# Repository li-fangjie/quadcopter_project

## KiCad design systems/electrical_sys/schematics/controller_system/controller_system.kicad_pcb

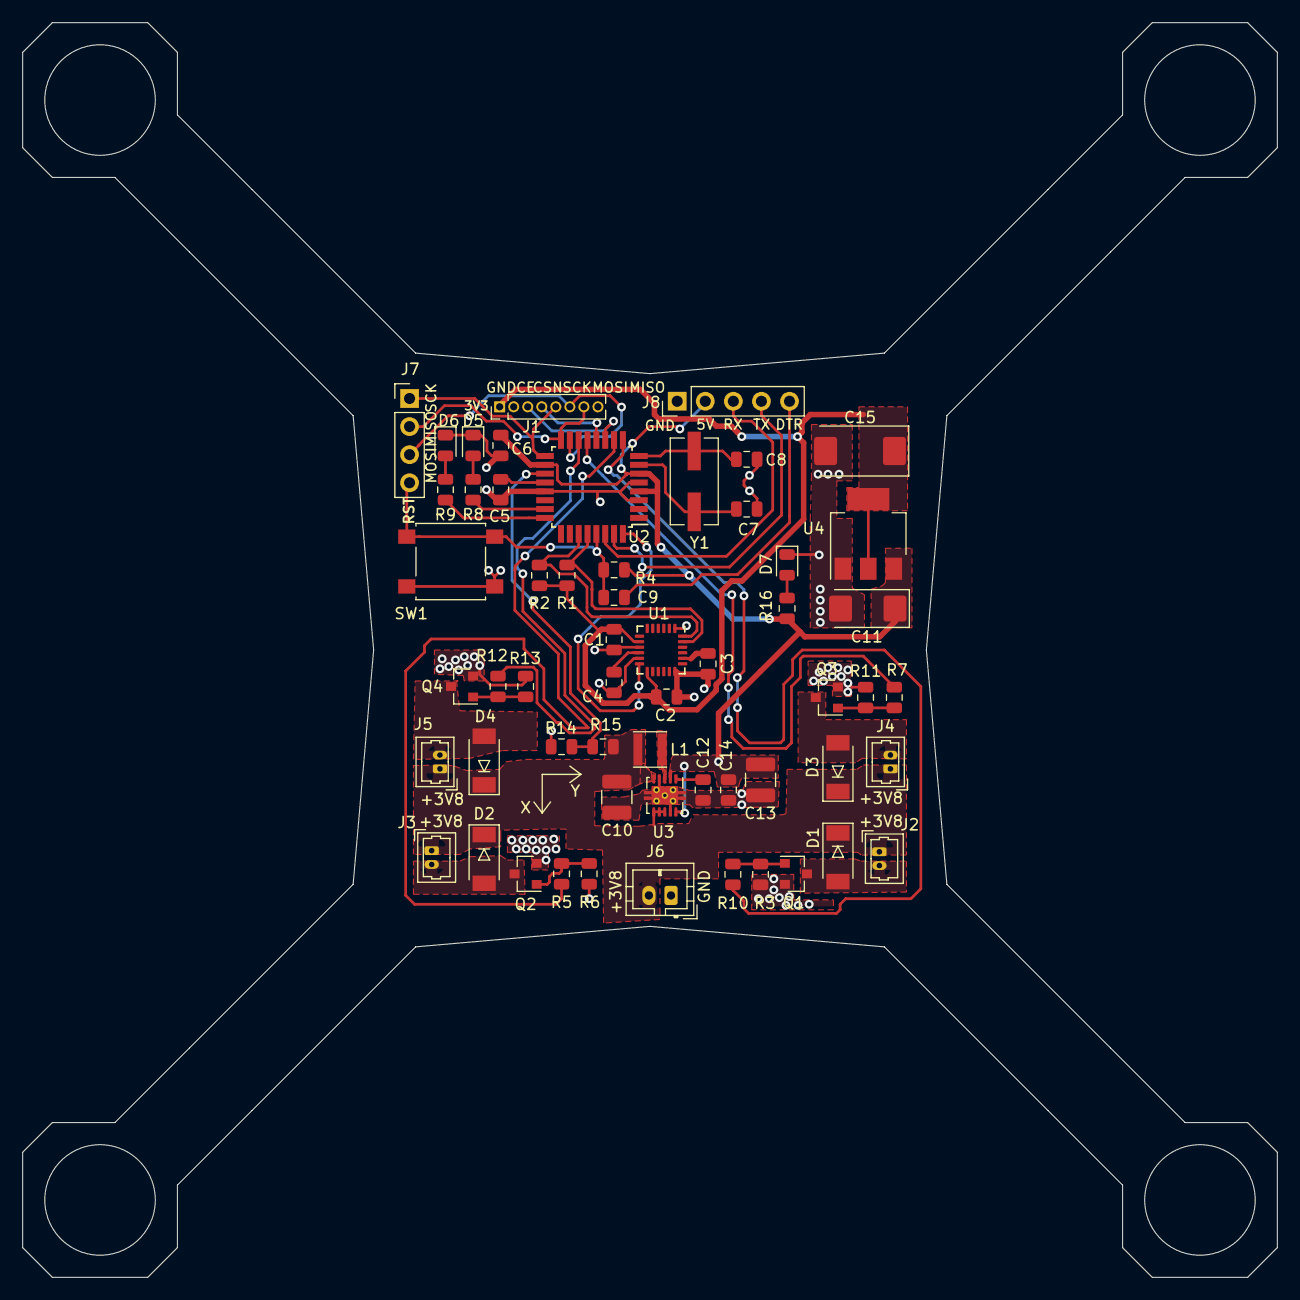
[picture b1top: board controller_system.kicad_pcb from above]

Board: 2 copper layers, 113.5 x 113.5 mm, 57 parts (0 on the bottom side), 41 nets.

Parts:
C1: 10 nF; C_0805_2012Metric
C2, C4, C5, C6, C9, C12, C14: 0.1 uF; C_0805_2012Metric
C3: 2.2 nF; C_0805_2012Metric
C7, C8: 22 pF; C_0805_2012Metric
C10: 10 uF; C_1210_3225Metric
C11: 10 uF; CP_EIA-6032-28_Kemet-C
C13: 22 uF; C_1210_3225Metric
C15: 22 uF; CP_EIA-7343-31_Kemet-D
D1, D2, D3, D4: D_Schottky; D_SOD-128
D5: LED_G; LED_0805_2012Metric
D6, D7: LED_R; LED_0805_2012Metric
J1: nRF24_Breakout; PinHeader_1x08_P1.27mm_Vertical
J2, J3, J4, J5: MOT; Molex_PicoBlade_53047-0210_1x02_P1.25mm_Vertical
J6: Lipo_Bat_Con; JST_PH_B2B-PH-K_1x02_P2.00mm_Vertical
J7: SPI_Conn_01x04; PinHeader_1x04_P2.54mm_Vertical
J8: FTDI_Conn_01x05; PinHeader_1x05_P2.54mm_Vertical
L1: 4.7 uH; L_Taiyo-Yuden_NR-30xx
Q1, Q2, Q3, Q4: Q_NMOS_GSD; SOT-23
R1, R2: 4.7 K; R_0805_2012Metric
R3, R4, R6, R11, R13: 10 K; R_0805_2012Metric
R5, R7, R10, R12: 100; R_0805_2012Metric
R8, R9, R16: 330; R_0805_2012Metric
R14, R15: 100 K; R_0805_2012Metric
SW1: MCU_RESET_SW; SW_SPST_B3S-1000
U1: MPU-6050; InvenSense_QFN-24_4x4mm_P0.5mm
U2: ATmega328P-AU; TQFP-32_7x7mm_P0.8mm
U3: TPS61202DRC; Texas_S-PVSON-N10_ThermalVias
U4: LM1117-3.3; SOT-223-3_TabPin2
Y1: 16 MHz; Crystal_SMD_ECS_CSM3X-2Pin_7.6x4.1mm

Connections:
+3V3: C1.1, C2.2, C15.1, J1.1, R1.1, R2.1, U1.8, U1.13, U4.2
+3V8: C10.1, D1.1, D2.1, D3.1, D4.1, J2.1, J3.1, J4.1, J5.1, J6.2, L1.1, R15.2, U3.5, U3.6, U3.7, U3.8
+5V: C6.1, C11.1, C13.1, C14.1, J8.2, R4.1, R16.2, U2.4, U2.6, U2.18, U3.2, U3.10, U4.3
/BAT_VAL: R14.2, R15.1, U2.19
/INT: U1.12, U2.32
/MCU/DTR: C9.2, J8.5
/MCU/FCS_LED_0: R8.2, U2.23
/MCU/FCS_LED_1: R9.2, U2.24
/MCU/RESET: C9.1, J7.4, R4.2, SW1.1, U2.29
/MCU/RXI: J8.3, U2.30
/MCU/TXO: J8.4, U2.31
/PWM_0: R10.2, U2.9
/PWM_1: R5.2, U2.10
/PWM_2: R12.2, U2.14
/PWM_3: R7.2, U2.13
/RF_CE: J1.3, U2.11
/RF_CSN: J1.4, U2.12
/SCL: R1.2, U1.23, U2.28
/SDA: R2.2, U1.24, U2.27
/SPI_MISO: J1.7, J7.2, U2.16
/SPI_MOSI: J1.6, J7.3, U2.15
/SPI_SCK: J1.5, J7.1, U2.17
GND: C1.2, C2.1, C3.1, C4.1, C5.2, C6.2, C7.1, C8.1, C10.2, C11.2, C12.2, C13.2, C14.2, C15.2, D5.1, D6.1, D7.1, J1.2, J6.1, J8.1, Q1.2, Q2.2, Q3.2, Q4.2, R3.1, R6.1, R11.1, R13.1, R14.1, SW1.2, U1.1, U1.9, U1.11, U1.18, U2.3, U2.5, U2.21, U3.4, U3.9, U3.11, U4.1
unnamed: C3.2, U1.20
unnamed: C4.2, U1.10
unnamed: C5.1, U2.20
unnamed: C7.2, U2.7, Y1.1
unnamed: C8.2, U2.8, Y1.2
unnamed: C12.1, U3.1
unnamed: D1.2, J2.2, Q1.3
unnamed: D2.2, J3.2, Q2.3
unnamed: D3.2, J4.2, Q3.3
unnamed: D4.2, J5.2, Q4.3
unnamed: D5.2, R8.1
unnamed: D6.2, R9.1
unnamed: D7.2, R16.1
unnamed: L1.2, U3.3
unnamed: Q1.1, R3.2, R10.1
unnamed: Q2.1, R5.1, R6.2
unnamed: Q3.1, R7.1, R11.2
unnamed: Q4.1, R12.1, R13.2

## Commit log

2020-03-23 First ever commit
2020-04-10 First commit; Mainly working through the control systems; Also uploaded the old circuit diagrams; TODO: finish the central FCS and module integration; Start hardware and circuitry assembly
2020-04-10 implemented template support for the pid systems
2020-04-19 integraded the FCS; TODO: testing
2021-01-20 just updating everything from last summer
